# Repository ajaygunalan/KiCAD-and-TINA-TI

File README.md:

# KiCAD-and-TINA-TI

This repo containes my notes, PCB design, TINA-TI for my PhD course, "Electronics & Circuits" by Marco Sartore

- week1 - opamps
- week2 - adc, dac
- week3 - ? 
- week4 - pcb design using KiCad

References for KiCad Library:

1. [KiCad Libraries ](https://kicad.github.io/packages3d/)
2. [KiCad Packages3D](https://gitlab.com/kicad/libraries/kicad-packages3D)

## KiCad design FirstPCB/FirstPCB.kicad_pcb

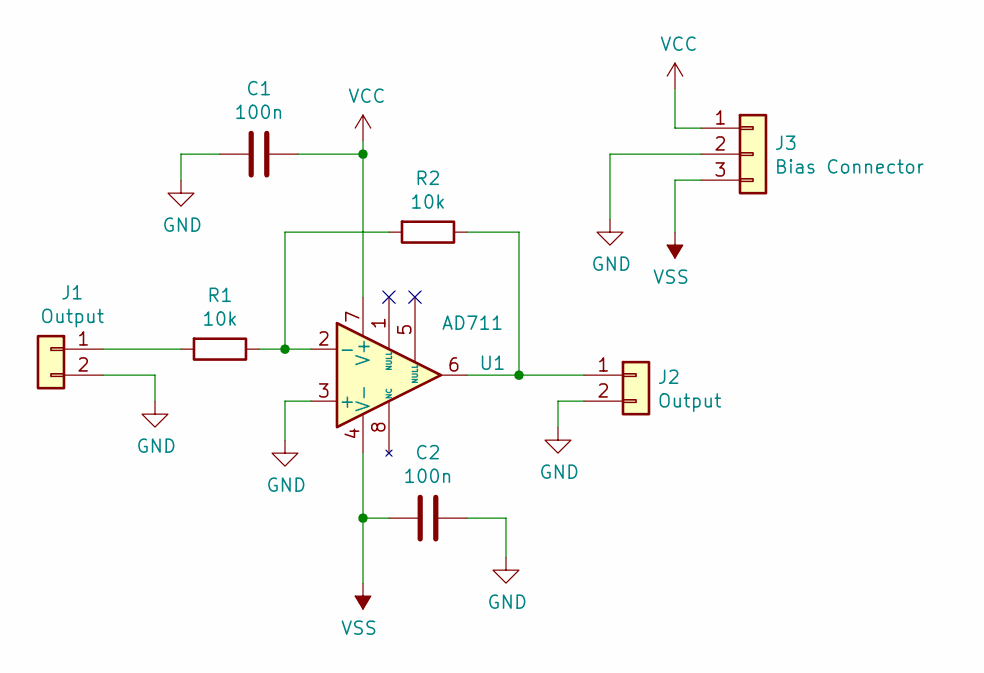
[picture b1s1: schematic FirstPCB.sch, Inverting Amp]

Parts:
C1, C2: 100n; C_Radial_D5.0mm_H5.0mm_P2.00mm
J1, J2: Output; PinHeader_1x02_P2.54mm_Vertical
J3: Bias Connector; PinHeader_1x03_P2.54mm_Vertical
R1, R2: 10k; R_Axial_DIN0207_L6.3mm_D2.5mm_P7.62mm_Horizontal
U1: AD711; AD711_PDIP; Digikey AD711JNZ-ND

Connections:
GND: C1.2, C2.1, J1.2, J2.2, J3.2, U1.3 (+)
unnamed: J1.1, R1.2
unnamed: J2.1, R2.1, U1.6
unnamed: R1.1, R2.2, U1.2 (-)
VCC: C1.1, J3.1, U1.7 (V+)
VSS: C2.2, J3.3, U1.4 (V-)

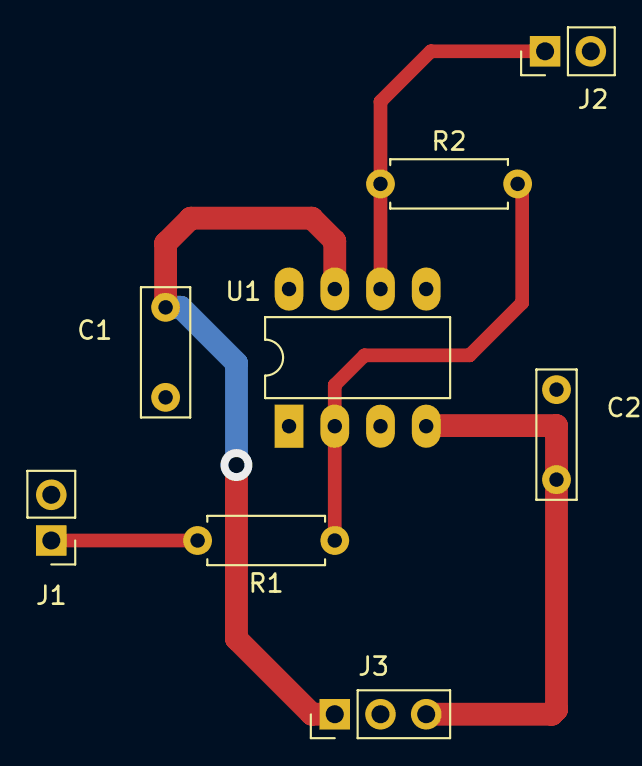
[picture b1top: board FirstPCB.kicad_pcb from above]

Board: 2 copper layers, 8 parts (0 on the bottom side), 6 nets.

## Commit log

2021-06-10 added footprint for AD711
2021-06-11 rough PCB design done
2021-06-11 rough PCB optimised
2021-06-11 First PCB done with margin and mouting screws
2021-06-11 added ref lib for KiCAD
2021-06-11 added TINI-TI and Obsidian Notes
